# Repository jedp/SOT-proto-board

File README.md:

# SOT23-6 proto board

For when you want to use a breadboard with SOT components.

0.5 inches across.

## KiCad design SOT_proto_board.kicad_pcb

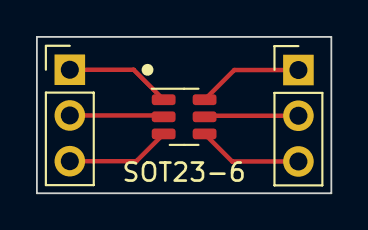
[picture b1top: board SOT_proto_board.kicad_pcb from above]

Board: 2 copper layers, 16.4 x 8.7 mm, 3 parts (0 on the bottom side), 6 nets.

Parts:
J1, J2: Conn_01x03_Female; PinHeader_1x03_P2.54mm_Vertical
U1: LTC4440ES6; SOT-23-6

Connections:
unnamed: J1.1, U1.1 (VCC)
unnamed: J1.2, U1.2 (GND)
unnamed: J1.3, U1.3 (INP)
unnamed: J2.1, U1.6 (BOOST)
unnamed: J2.2, U1.5 (TG)
unnamed: J2.3, U1.4 (TS)

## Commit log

2023-12-06 SOT23-6 proto board
